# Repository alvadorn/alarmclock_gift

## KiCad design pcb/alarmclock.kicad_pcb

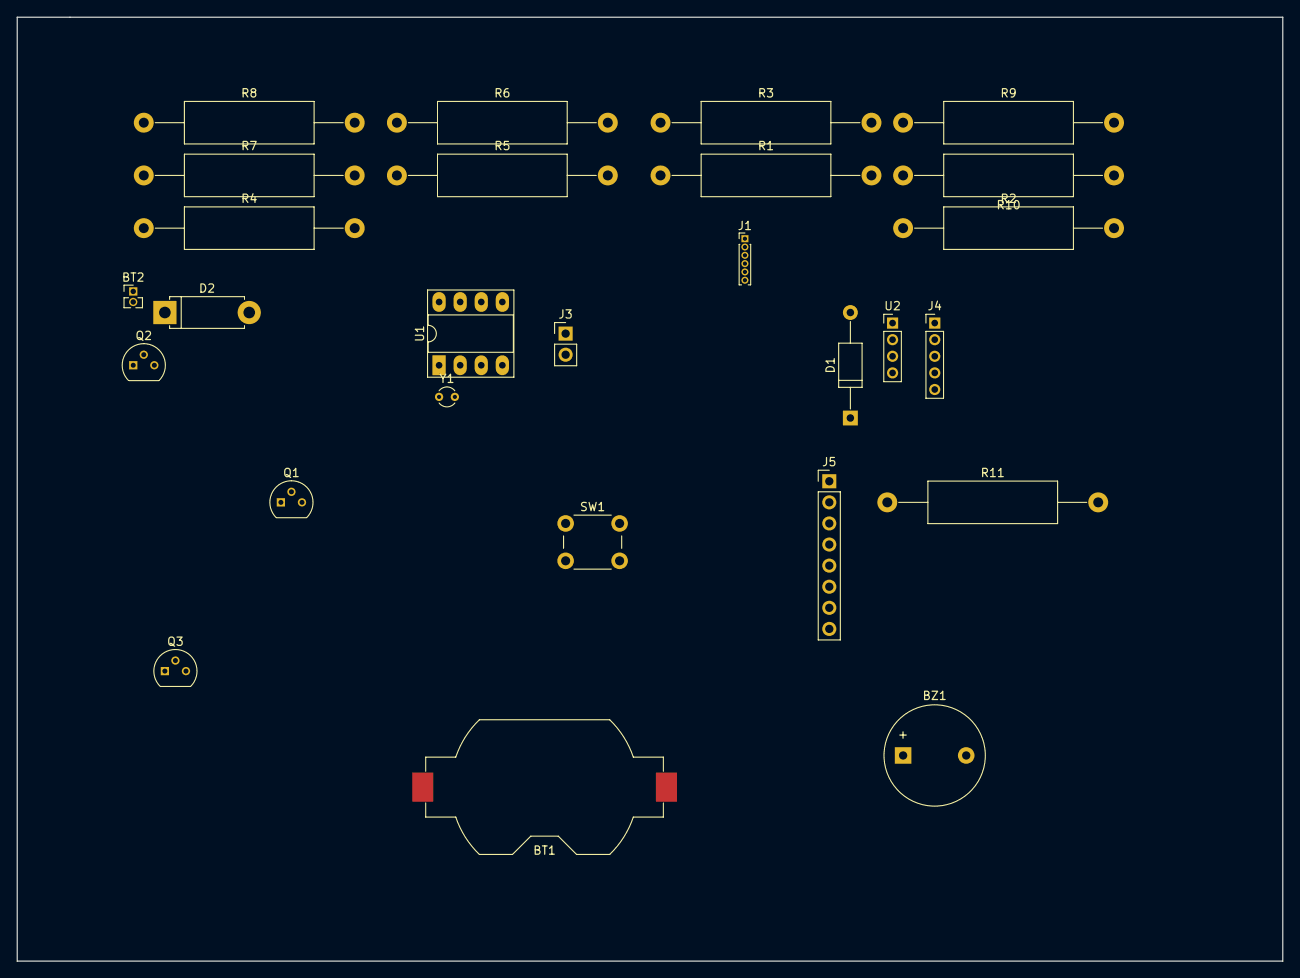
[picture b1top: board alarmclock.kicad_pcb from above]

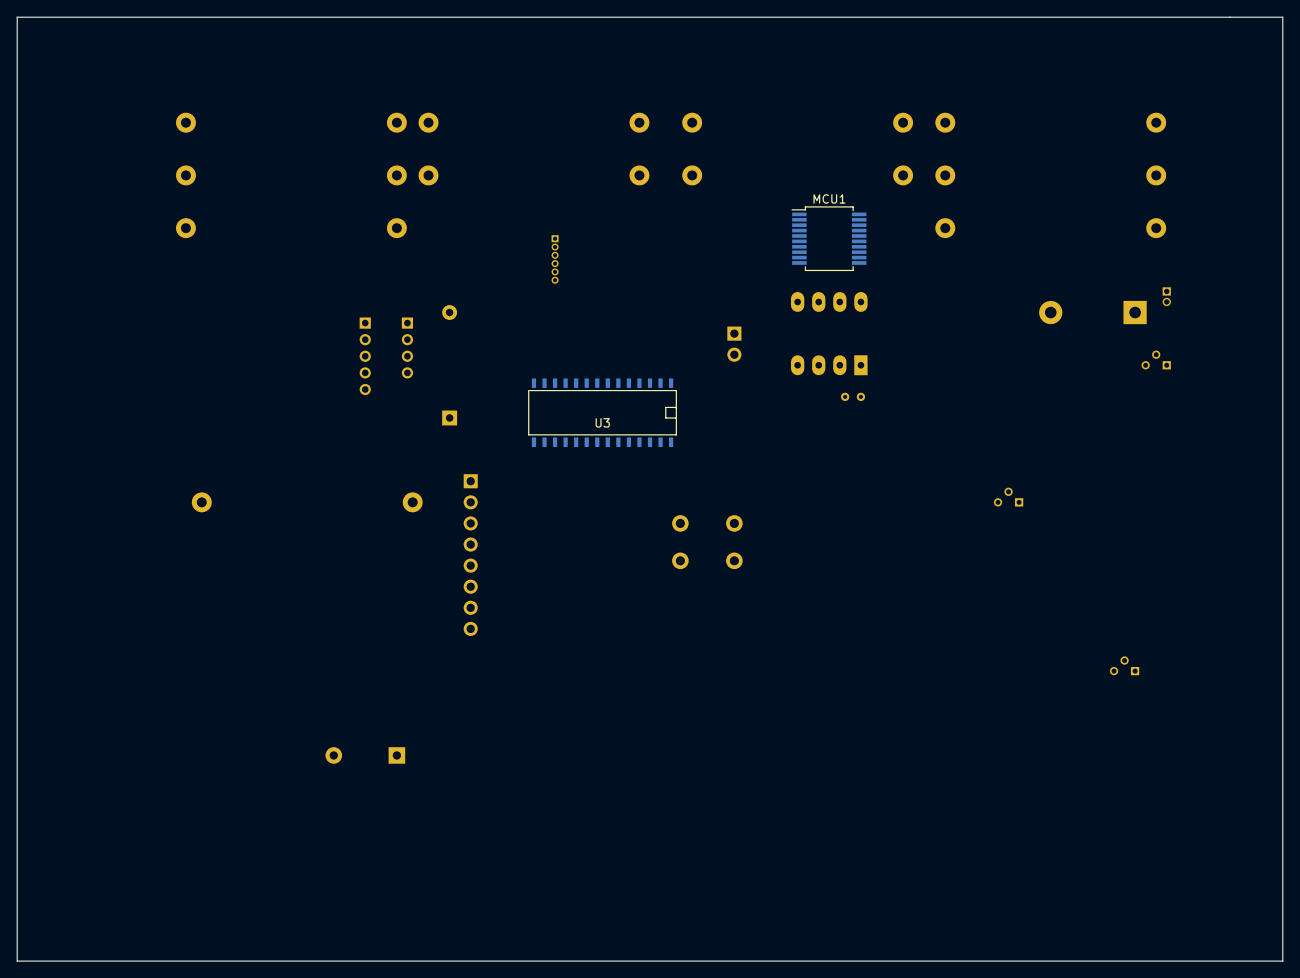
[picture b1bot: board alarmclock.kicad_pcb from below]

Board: 2 copper layers, 152.4 x 113.7 mm, 29 parts (2 on the bottom side), 27 nets, no tracks yet.

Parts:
BT1: CR2032; Keystone_1058_1x2032-CoinCell
BT2: 6V; Pin_Header_Straight_1x02_Pitch1.27mm
BZ1: Buzzer; Buzzer_12x9.5RM7.6
D1: 2.7V; D_A-405_P12.70mm_Horizontal
D2: D; D_5W_P10.16mm_Horizontal
J1: Conn_01x06_Male; Pin_Header_Straight_1x06_Pitch1.00mm
J3: Conn_01x02_Female; Pin_Header_Straight_1x02_Pitch2.54mm
J4: Conn_01x05_Female; Pin_Header_Straight_1x05_Pitch2.00mm
J5: Conn_01x08_Male; Pin_Header_Straight_1x08_Pitch2.54mm
MCU1: PIC18F14K50-E/SS; SSOP-20_5.3x7.2mm_Pitch0.65mm
Q1, Q2, Q3: BC547; TO-92_Molded_Narrow
R1, R3: 1K; R_Axial_DIN0516_L15.5mm_D5.0mm_P25.40mm_Horizontal
R2: 120; R_Axial_DIN0516_L15.5mm_D5.0mm_P25.40mm_Horizontal
R4, R5, R6, R7, R8, R11: 10K; R_Axial_DIN0516_L15.5mm_D5.0mm_P25.40mm_Horizontal
R9, R10: 4K7; R_Axial_DIN0516_L15.5mm_D5.0mm_P25.40mm_Horizontal
SW1: SW_Push; SW_PUSH_6mm
U1: DS1307+; DIP-8_W7.62mm_Socket_LongPads
U2: DHT11; Pin_Header_Straight_1x04_Pitch2.00mm
U3: MCP23017; SOIC-28
Y1: 32.7kHz; Crystal_Round_d2.0mm_Vertical

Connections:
3.3V: D1.1, J5.1, Q1.1, Q2.1, R2.1
5.5V: D2.1, MCU1.1, R4.1, R5.1, R6.1, R7.1, R8.1, R9.1, R10.1, R11.2, U1.8, U2.1, U3.9
6V: BT2.1, BZ1.1, D2.2, R2.2
BTN_CENTER: J4.5, MCU1.14, R4.2
BTN_DOWN: J4.3, MCU1.16, R6.2
BTN_LEFT: J4.4, MCU1.15, R5.2
BTN_RIGHT: J1.5, J4.2, MCU1.18, R7.2
BTN_UP: J1.4, J4.1, MCU1.19, R8.2
BUZZER: MCU1.10, R3.2
DC: J5.5, MCU1.6
DHT: MCU1.9, U2.2
GND: BT1.2, BT2.2, J3.2, J5.2, MCU1.12, MCU1.17, MCU1.20, Q1.3, Q2.3, Q3.3, SW1.1, U1.4, U2.4, U3.10
LED_CONTROL: MCU1.8, R1.2
MCLR: J1.1, MCU1.4, R11.1, SW1.2
unnamed: BT1.1, U1.3
unnamed: BZ1.2, Q3.1
unnamed: D1.2, Q2.2
unnamed: Q1.2, R1.1
unnamed: Q3.2, R3.1
unnamed: U1.1, Y1.1
unnamed: U1.2, Y1.2
PGM: J1.6, J5.7, MCU1.7
RESET: J5.4, MCU1.2
SCE: J5.3, MCU1.3
SDIN: J5.6, MCU1.5
scl: MCU1.11, R10.2, U1.6
sda: MCU1.13, R9.2, U1.5

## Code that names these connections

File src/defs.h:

#ifndef __DEFS_H__
#define __DEFS_H__


#include <xc.h>
#include <pic18f14k50.h>


// CONFIG1L
#pragma config CPUDIV=NOCLKDIV
#pragma config USBDIV=OFF


// CONFIG1H
#pragma config FOSC=IRC

// CONFIG2L
#pragma config BOREN=NOSLP
#pragma config BORV=30

// CONFIG2H
#pragma config WDTEN=ON
#pragma config WDTPS=32768

// CONFIG3H
#pragma config HFOFST=OFF
#pragma config MCLRE=ON



#define _XTAL_FREQ 8000000 // 2 MHz

#define NULL 0
typedef unsigned char byte;


// pins
// lcd pins
#define lcd_clk LATCbits.LC3
#define lcd_dc LATCbits.LC4
#define lcd_din LATCbits.LC5
#define lcd_led LATCbits.LC6 
#define lcd_sce LATAbits.LA4
#define lcd_rst LATAbits.LA5

// button pins
#define btn_up PORTAbits.RA0 
#define btn_right PORTAbits.RA1 
#define btn_down PORTCbits.RC0
#define btn_left PORTCbits.RC1
#define btn_center PORTCbits.RC2

// DHT pins
#define dht_read PORTCbits.RC7
#define dht_write LATCbits.LC7
#define dht_mode TRISCbits.TRISC7

// buzzer
#define buzzer LATBbits.LB5


#endif

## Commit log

2018-02-26 Initialized repository
2018-02-26 Drawing schematic
2018-02-26 Schematic done
2018-02-27 Definitions about pins, clocks
2018-02-27 Initial settings functions
2018-02-27 SPI related
2018-02-27 Initial configuration
2018-02-27 Makefile changes
2018-02-27 Some adjustments in schematic
2018-02-27 Basic functions of lcd implemented
2018-02-27 Configuration bits
2018-02-27 Manual optimization in sending MSB bit
2018-02-27 SPI not needed, only I2C
2018-02-27 Makefile generating map
2018-02-28 Header from Electronic Wings with basic modifications
2018-02-28 Writing strings to LCD
2018-02-28 Preparing for loop
